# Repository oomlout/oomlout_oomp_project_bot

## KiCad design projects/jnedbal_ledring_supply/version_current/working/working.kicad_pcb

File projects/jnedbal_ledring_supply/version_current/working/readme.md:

# LEDring_supply by jnedbal  
This is a harvested standardized copy of a project from github.  
The original project can be found at:  
https://github.com/jnedbal/LEDring_supply  
Please consult that link for additional, details, files, and license information.  
Note: It was auto harvested and if the original repo had more than one board file or anything out of the ordinary the files here are likely not representative.

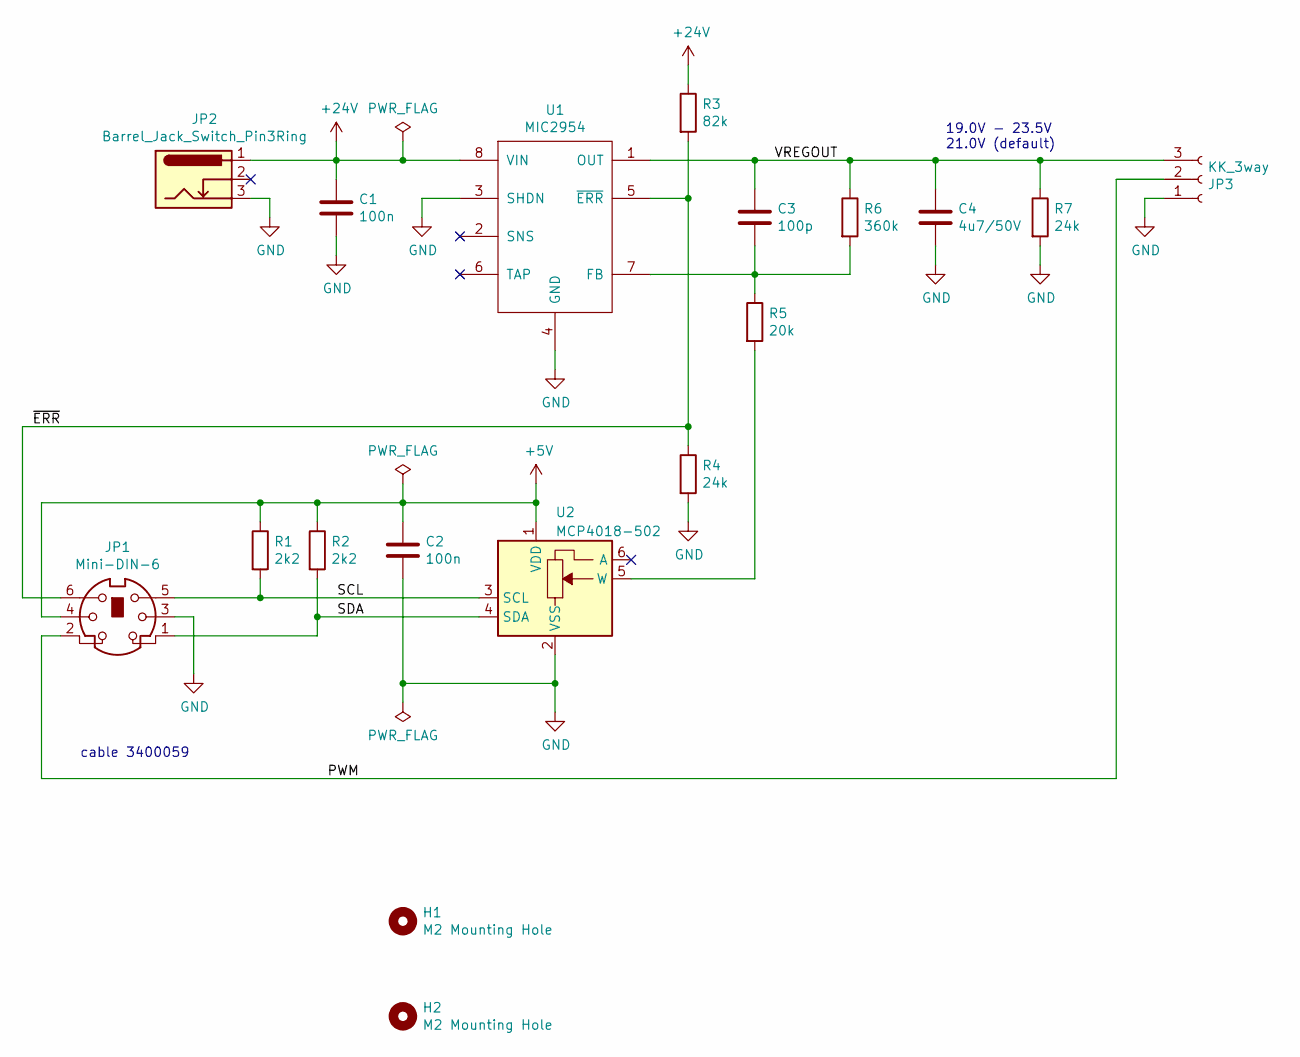
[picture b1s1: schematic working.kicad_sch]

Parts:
C1, C2: 100n; C_0603_1608Metric; Part Number MC0603B104K500CT
C3: 100p; C_0603_1608Metric; Part Number MC0603B101K500CT
C4: 4u7/50V; C_1206_3216Metric; Part Number GRM31CR71H475KA12L
H1, H2: M2 Mounting Hole; MountingHole_2.2mm_M2
JP1: Mini-DIN-6; MiniDIN6way; Part Number PSG01567
JP2: Barrel_Jack_Switch_Pin3Ring; 2.1mmBarrelJackTop; Part Number FC681473
JP3: KK_3way; Molex_KK-254_AE-6410-03A_1x03_P2.54mm_Vertical; Part Number 22-27-2031
R1, R2: 2k2; R_0603_1608Metric; Part Number MCWR06X2201FTL
R3: 82k; R_0603_1608Metric; Part Number MCWR06X8202FTL
R4: 24k; R_0603_1608Metric; Part Number MCWR06X2002FTL
R5: 20k; R_0603_1608Metric; Part Number MCWR06X2002FTL
R6: 360k; R_0603_1608Metric; Part Number MCWR06X3603FTL
R7: 24k; R_0603_1608Metric; Part Number MCWR06X2402FTL
U1: MIC2954; SO-8_3.9x4.9mm_P1.27mm; Part Number MIC2954-08YM
U2: MCP4018-502; SOT-363_SC-70-6; Part Number MCP4018T-502E/LT

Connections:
+5V: C2.1, JP1.4, R1.1, R2.1, U2.1 (VDD)
+24V: C1.1, JP2.1, R3.1, U1.8 (VIN)
/PWM: JP1.2, JP3.2
/SCL: JP1.5, R1.2, U2.3 (SCL)
/SDA: JP1.1, R2.2, U2.4 (SDA)
/VREGOUT: C3.1, C4.1, JP3.3, R6.1, R7.1, U1.1 (OUT)
/~ERR: JP1.6, R3.2, R4.1, U1.5 (~ERR)
GND: C1.2, C2.2, C4.2, JP1.3, JP2.3, JP3.1, R4.2, R7.2, U1.3 (SHDN), U1.4 (GND), U2.2 (VSS)
unnamed: C3.2, R5.1, R6.2, U1.7 (FB)
unnamed: R5.2, U2.5 (W)

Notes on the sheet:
19.0V - 23.5V 21.0V (default)
cable 3400059

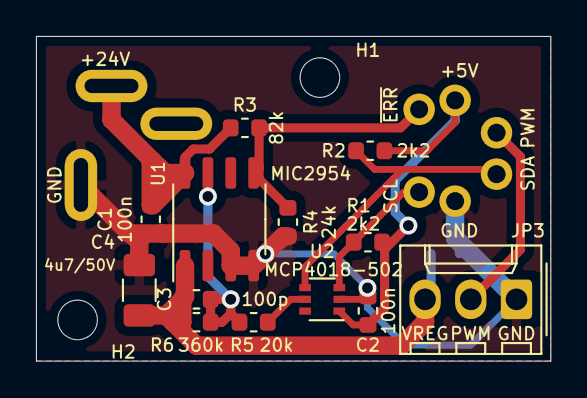
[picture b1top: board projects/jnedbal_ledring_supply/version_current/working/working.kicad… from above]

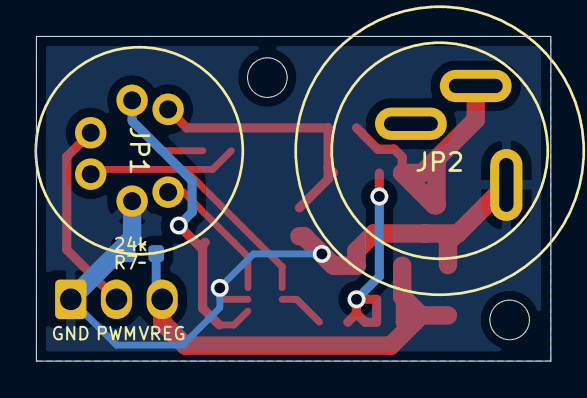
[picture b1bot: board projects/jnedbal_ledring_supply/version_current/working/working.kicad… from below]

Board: 2 copper layers, 28.6 x 18.0 mm, 18 parts (3 on the bottom side), 10 nets.

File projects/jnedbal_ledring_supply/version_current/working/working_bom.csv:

"Id";"Designator";"Footprint";"Quantity";"Designation";"Supplier and ref";
1;"R2,R1";"R_0603_1608Metric";2;"2k2";;;
2;"JP3";"Molex_KK-254_AE-6410-03A_1x03_P2.54mm_Vertical";1;"KK_3way";;;
3;"R7,R4";"R_0603_1608Metric";2;"24k";;;
4;"JP1";"MiniDIN6way";1;"Mini-DIN-6";;;
5;"C1,C2";"C_0603_1608Metric";2;"100n";;;
6;"C3";"C_0603_1608Metric";1;"100p";;;
7;"C4";"C_1206_3216Metric";1;"4u7/50V";;;
8;"JP2";"2.1mmBarrelJackTop";1;"Barrel_Jack_Switch_Pin3Ring";;;
9;"R3";"R_0603_1608Metric";1;"82k";;;
10;"R5";"R_0603_1608Metric";1;"20k";;;
11;"R6";"R_0603_1608Metric";1;"360k";;;
12;"U1";"SO-8_3.9x4.9mm_P1.27mm";1;"MIC2954";;;
13;"U2";"SOT-363_SC-70-6";1;"MCP4018-502";;;

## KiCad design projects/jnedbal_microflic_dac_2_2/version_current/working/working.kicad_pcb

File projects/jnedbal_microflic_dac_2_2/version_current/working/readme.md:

# OOMP Project  
## MicroFLiC_DAC_2_2  by jnedbal  
  
oomp key: oomp_projects_flat_jnedbal_microflic_dac_2_2  
(snippet of original readme)  

  full source readme at [readme_src.md](readme_src.md)  
  
source repo at: [https://github.com/jnedbal/MicroFLiC_DAC_2_2](https://github.com/jnedbal/MicroFLiC_DAC_2_2)  
## Board  

## Schematic  

[schematic pdf](working_schematic.pdf)  
## Images

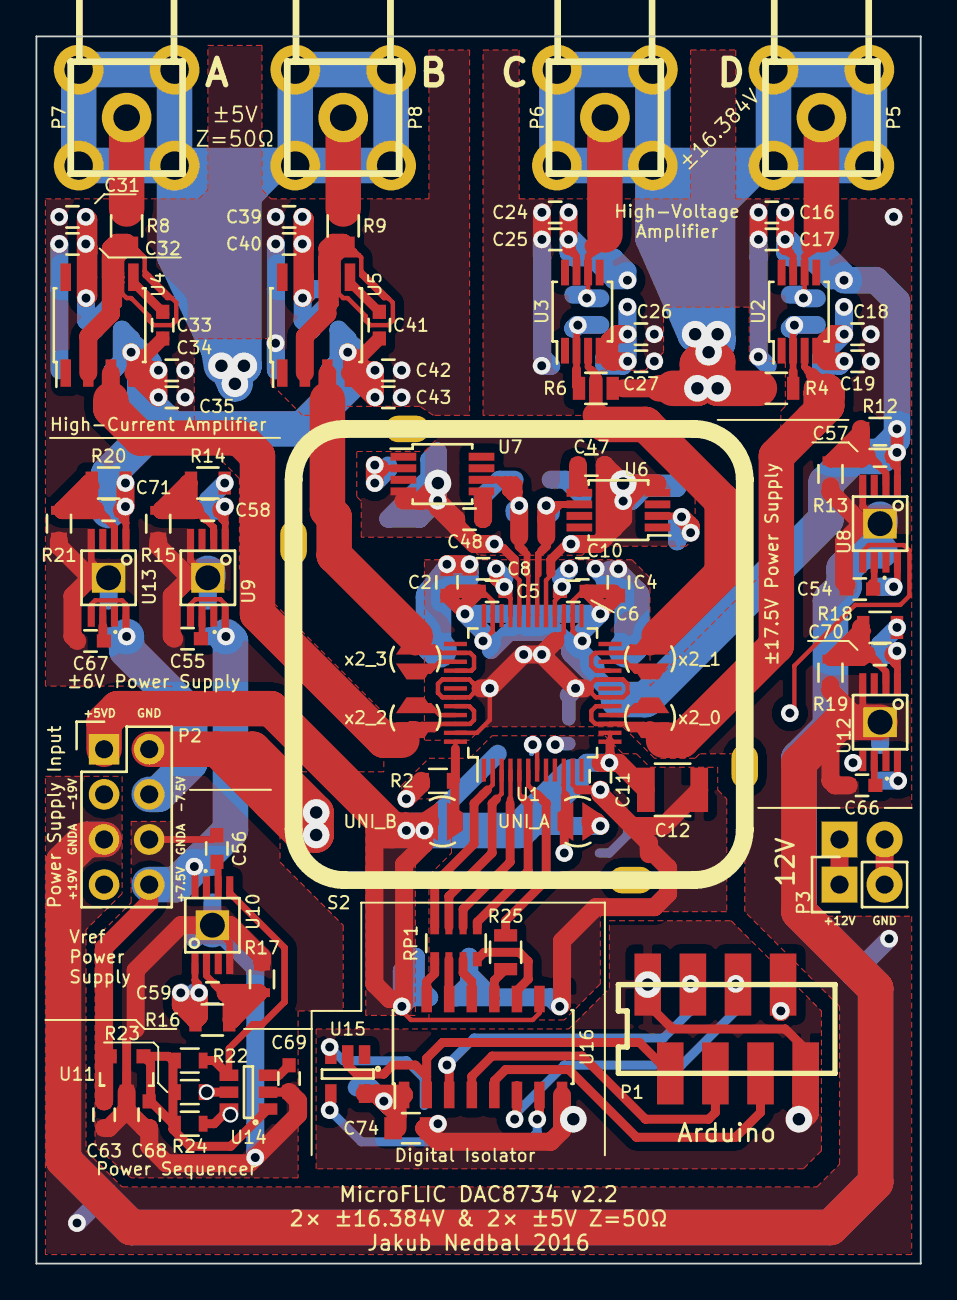
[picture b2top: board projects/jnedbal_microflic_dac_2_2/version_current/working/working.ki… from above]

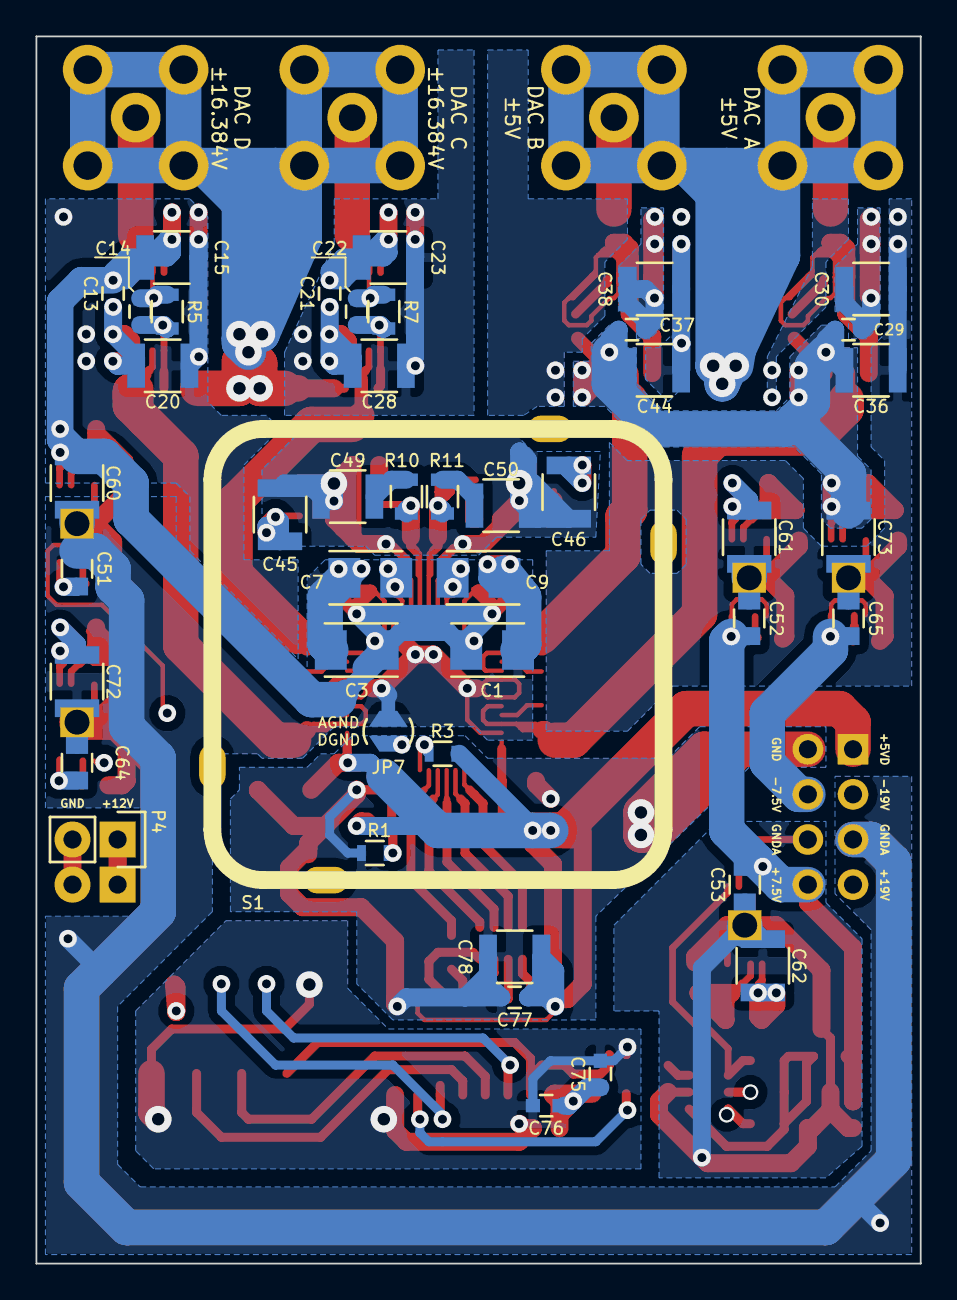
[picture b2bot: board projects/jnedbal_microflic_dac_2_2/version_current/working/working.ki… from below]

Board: 4 copper layers, 49.8 x 69.1 mm, 137 parts (45 on the bottom side), 74 nets.

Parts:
C1, C3, C7, C9: 4u7/25V; TantalC_SizeB_EIA-3528_Reflow
C2, C4, C8, C10, C11, C16, C19, C24, C27, C31, C35, C39, C43, C63, C68, C75, C76, C77: 100n; C_0603
C5, C6, C13, C17, C18, C21, C25, C26, C29, C32, C34, C37, C40, C42, C54, C55, C56, C57, C58, C59, C66, C67, C70, C71: 10n; C_0603
C12, C30, C36, C38, C44, C45, C46, C49, C50, C61, C62, C73, C78: 22u/25V; C_1210
C14, C22, C33, C41: 10p; C_0603
C15, C20, C23, C28, C60, C72: 10u/35V; C_1210
C47, C48, C69: 1u/25V; C_0603
C51, C52, C53, C64, C65, C74: 10u/25V; C_0805
JP1: UNI_A; solder_jumper
JP2: UNI_B; solder_jumper
JP3: x2_0; solder_jumper
JP4: x2_1; solder_jumper
JP5: x2_2; solder_jumper
JP6: x2_3; solder_jumper
JP7: GND/GNDA; solder_jumper
P1: 8-way Micro-MaTch; 7-188275-8
P2: 2x4 header strip; Pin_Header_Straight_2x04
P3: 1x2 header strip; Pin_Header_Straight_1x02
P4: 1x2 socket strip; Socket_Strip_Straight_1x02
P5, P6, P7, P8: SMA
R1, R2, R3, R13, R15, R17, R19, R21, R22, R23, R24: 12k; R_0603
R4, R5, R6, R7: 1k/0.01%/100mW; R_0805
R8, R9: 49R9/0.1%/250mW; R_0805
R10, R11: 1; R_0805
R12, R18: 165k; R_0805
R14, R16, R20: 48k7; R_0805
R25: 150; R_0805
RP1: 4x150; R_Array_Convex_4x0603
S1, S2: shield_can; can-MS257-10
U1: DAC8734; TQFP-48_7x7mm_Pitch0.5mm
U2, U3: OPA211; MSOP-8_3x3mm_Pitch0.65mm
U4, U5: AD8021; SOIC-8_3.9x4.9mm_Pitch1.27mm
U6: REF5040; MSOP-8_3x3mm_Pitch0.65mm
U7: REF5050; MSOP-8_3x3mm_Pitch0.65mm
U8, U9, U10: TPS7A4901; SSOP8_powerPAD
U11: LM3480; SOT-23
U12, U13: TPS7A3001; SSOP8_powerPAD
U14: LM3880; SOT-23-6
U15: 74AHC1G14; SOT-23-5
U16: Si8651; SOIC-16_3.9x9.9mm_Pitch1.27mm

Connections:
+5V: C68.1, R22.2, R23.2, R24.2, U11.1, U14.1
+5VD: C11.1, C12.1, C77.1, C78.1, JP1.2, JP2.2, P2.1, R3.2, U1.13, U1.14, U16.10, U16.16
+6V: C29.1, C30.2, C31.2, C32.2, C37.1, C38.2, C39.2, C40.2, C58.1, C61.1, R14.1, U4.7, U5.7, U9.1
-6V: C29.2, C33.2, C34.2, C35.2, C36.2, C37.2, C41.2, C42.2, C43.2, C44.2, C71.1, C73.1, R20.1, U4.4, U5.4, U13.1
/P12V: P3.1, P4.1
/PGND: P3.2, P4.2
/digitalIsolation/A_GND: C74.2, C75.2, C76.2, P1.1, P1.8, U15.3, U16.8
/digitalIsolation/A_IOREF: C74.1, C75.1, C76.1, P1.7, U15.5, U16.1
/digitalIsolation/A_SCLK: P1.3, U16.3
/digitalIsolation/A_SDI: P1.4, U16.4
/digitalIsolation/A_SDO: P1.5, U16.6
/digitalIsolation/A_~LDAC: P1.6, U16.5
/digitalIsolation/A_~SS: P1.2, U15.2, U16.2
/digitalIsolation/SCLK: RP1.7, U1.3
/digitalIsolation/SDI: RP1.6, U1.4
/digitalIsolation/SDO: RP1.5, U1.5
/digitalIsolation/~LDAC: R25.1, U1.6
/digitalIsolation/~SS: RP1.8, U1.2
/highCurrentAmp/CMP1: C41.1, U5.5
/highCurrentAmp/CMP2: C33.1, U4.5
/highCurrentAmp/INV-2: R8.2, U4.2, U4.6
/highCurrentAmp/INV-3: R9.2, U5.2, U5.6
/highCurrentAmp/VOUT-2: JP5.2, U1.44, U1.46, U4.3
/highCurrentAmp/VOUT-3: JP6.2, U1.38, U1.40, U5.3
/highCurrentAmp/VOUT-C: P7.1, R8.1
/highCurrentAmp/VOUT-D: P8.1, R9.1
/highVoltageAmp/INV-0: C14.2, R4.1, R5.2, U2.2
/highVoltageAmp/INV-1: C22.2, R6.1, R7.2, U3.2
/highVoltageAmp/VOUT-0: JP3.2, U1.15, U1.17, U2.3
/highVoltageAmp/VOUT-1: JP4.2, U1.21, U1.23, U3.3
/highVoltageAmp/VOUT-A: C14.1, P5.1, R5.1, U2.6
/highVoltageAmp/VOUT-B: C22.1, P6.1, R7.1, U3.6
/powerSupply/+7.5V: C52.1, C53.1, C63.1, P2.8, U9.5, U9.8, U10.8, U11.2
/powerSupply/+19V: C51.1, P2.7, U8.8
/powerSupply/-7.5V: C65.1, P2.4, U13.5, U13.8
/powerSupply/-19V: C64.1, P2.3, U12.8
/powerSupply/EN_REF: R22.1, U10.5, U14.4
/powerSupply/EN_VDD: R23.1, U8.5, U14.5
/powerSupply/EN_VSS: R24.1, U12.5, U14.6
/powerSupply/FB+6: C58.2, R14.2, R15.1, U9.2
/powerSupply/FB-6: C71.2, R20.2, R21.1, U13.2
/powerSupply/FBREF: C59.2, R16.2, R17.1, U10.2
/powerSupply/FBVDD: C57.2, R12.2, R13.1, U8.2
/powerSupply/FBVSS: C70.2, R18.2, R19.1, U12.2
/powerSupply/NR+6: C55.1, U9.6
/powerSupply/NR-6: C67.1, U13.6
/powerSupply/NRREF: C56.1, U10.6
/powerSupply/NRVDD: C54.1, U8.6
/powerSupply/NRVSS: C66.1, U12.6
/reference/4.096V: R10.1, U1.30, U6.6
/reference/5.000V: R11.1, U1.31, U7.6
/reference/TRIM4: C47.1, U6.5
/reference/TRIM5: C48.1, U7.5
GND: C11.2, C12.2, C77.2, C78.2, JP7.1, P2.2, R1.2, R2.2, U1.11, U16.9
GNDA: C1.2, C2.2, C3.2, C4.2, C7.1, C8.2, C9.1, C10.2, C15.1, C16.1, C17.1, C18.1, C19.1, C20.1, C23.1, C24.1, C25.1, C26.1, C27.1, C28.1, C30.1, C31.1, C32.1, C34.1, C35.1, C36.1, C38.1, C39.1, C40.1, C42.1, C43.1, C44.1, C45.2, C46.2, C47.2, C48.2, C49.2, C50.2, C51.2, C52.2, C53.2, C54.2, C55.2, C56.2, C60.2, C61.2, C62.2, C63.2, C64.2, C65.2, C66.2, C67.2, C68.2, C69.2, C72.2, C73.2, JP7.2, P2.5, P2.6, P5.2, P5.3, P5.4, P5.5, P6.2, P6.3, P6.4, P6.5, P7.2, P7.3, P7.4, P7.5, P8.2, P8.3, P8.4, P8.5, R4.2, R6.2, R13.2, R15.2, R17.2, R19.2, R21.2, S1.1, S2.2, U1.18, U1.20, U1.27, U1.29, U1.32, U1.41, U1.43, U1.47, U6.4, U7.4, U8.4, U8.9, U9.4, U9.9, U10.4, U10.9, U11.3, U12.4, U12.9, U13.4, U13.9, U14.2
unnamed: C49.1, R10.2
unnamed: C50.1, R11.2
unnamed: C69.1, U14.3
unnamed: JP1.1, R1.1, U1.10
unnamed: JP2.1, R2.1, U1.48
unnamed: JP3.1, U1.16
unnamed: JP4.1, U1.22
unnamed: JP5.1, U1.45
unnamed: JP6.1, U1.39
unnamed: R3.1, U1.7
unnamed: R25.2, U16.12
unnamed: RP1.1, U16.15
unnamed: RP1.2, U16.14
unnamed: RP1.3, U16.13
unnamed: RP1.4, U16.11
unnamed: U15.4, U16.7
VCC: C45.1, C46.1, C59.1, C62.1, R16.1, U6.2, U7.2, U10.1
VDD: C1.1, C2.1, C3.1, C4.1, C5.1, C6.1, C13.1, C15.2, C16.2, C17.2, C21.1, C23.2, C24.2, C25.2, C57.1, C60.1, R12.1, U1.26, U1.35, U2.7, U3.7, U8.1
VSS: C5.2, C6.2, C7.2, C8.1, C9.2, C10.1, C13.2, C18.2, C19.2, C20.2, C21.2, C26.2, C27.2, C28.2, C70.1, C72.1, R18.1, U1.28, U1.33, U2.4, U3.4, U12.1

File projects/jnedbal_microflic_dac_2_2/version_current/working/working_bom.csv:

"Id";"Designator";"Footprint";"Quantity";"Designation";"Supplier and ref";
1;"P5,P6,P7,P8";"SMA";4;"SMA";;;
2;"U12,U13";"SSOP8_powerPAD";2;"TPS7A3001";;;
3;"C54,C56,C59,C57,C70,C66,C18,C13,C17,C25,C34,C29,C32,C40,C5,C6,C21,C37,C42,C55,C58,C67,C71,C26";"C_0603";24;"10n";;;
4;"C53,C51,C64,C52,C65,C74";"C_0805";6;"10u/25V";;;
5;"R16,R14,R20";"R_0805";3;"48k7";;;
6;"U10,U8,U9";"SSOP8_powerPAD";3;"TPS7A4901";;;
7;"C62,C36,C30,C12,C45,C46,C49,C50,C61,C73,C38,C44,C78";"C_1210";13;"22u/25V";;;
8;"C60,C72,C20,C15,C23,C28";"C_1210";6;"10u/35V";;;
9;"R12,R18";"R_0805";2;"165k";;;
10;"JP1";"solder_jumper";1;"UNI_A";;;
11;"P2";"Pin_Header_Straight_2x04";1;"2x4 header strip";;;
12;"C19,C16,C35,C31,C2,C4,C8,C10,C11,C24,C27,C39,C43,C77,C75,C63,C68,C76";"C_0603";18;"100n";;;
13;"U2,U3";"MSOP-8_3x3mm_Pitch0.65mm";2;"OPA211";;;
14;"R5,R4,R6,R7";"R_0805";4;"1k/0.01%/100mW";;;
15;"C14,C22,C33,C41";"C_0603";4;"10p";;;
16;"R8,R9";"R_0805";2;"49R9/0.1%/250mW";;;
17;"U4,U5";"SOIC-8_3.9x4.9mm_Pitch1.27mm";2;"AD8021";;;
18;"U7";"MSOP-8_3x3mm_Pitch0.65mm";1;"REF5050";;;
19;"P1";"7-188275-8";1;"8-way Micro-MaTch";;;
20;"U14";"SOT-23-6";1;"LM3880";;;
21;"U1";"TQFP-48_7x7mm_Pitch0.5mm";1;"DAC8734";;;
22;"U15";"SOT-23-5";1;"74AHC1G14";;;
23;"U16";"SOIC-16_3.9x9.9mm_Pitch1.27mm";1;"Si8651";;;
24;"C1,C3,C7,C9";"TantalC_SizeB_EIA-3528_Reflow";4;"4u7/25V";;;
25;"C47,C48,C69";"C_0603";3;"1u/25V";;;
26;"JP6";"solder_jumper";1;"x2_3";;;
27;"JP5";"solder_jumper";1;"x2_2";;;
28;"JP4";"solder_jumper";1;"x2_1";;;
29;"JP3";"solder_jumper";1;"x2_0";;;
30;"JP2";"solder_jumper";1;"UNI_B";;;
31;"U6";"MSOP-8_3x3mm_Pitch0.65mm";1;"REF5040";;;
32;"P3";"Pin_Header_Straight_1x02";1;"1x2 header strip";;;
33;"P4";"Socket_Strip_Straight_1x02";1;"1x2 socket strip";;;
34;"R10,R11";"R_0805";2;"1";;;
35;"RP1";"R_Array_Convex_4x0603";1;"4x150";;;
36;"R25";"R_0805";1;"150";;;
37;"JP7";"solder_jumper";1;"GND/GNDA";;;
38;"U11";"SOT-23";1;"LM3480";;;
39;"S1,S2";"can-MS257-10";2;"shield_can";;;
40;"R24,R22,R13,R15,R17,R23,R19,R21,R1,R2,R3";"R_0603";11;"12k";;;

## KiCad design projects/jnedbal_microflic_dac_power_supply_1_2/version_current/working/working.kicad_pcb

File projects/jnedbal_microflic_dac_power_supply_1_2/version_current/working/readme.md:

# OOMP Project  
## MicroFLiC_DAC_power_supply_1_2  by jnedbal  
  
oomp key: oomp_projects_flat_jnedbal_microflic_dac_power_supply_1_2  
(snippet of original readme)  

  full source readme at [readme_src.md](readme_src.md)  
  
source repo at: [https://github.com/jnedbal/MicroFLiC_DAC_power_supply_1_2](https://github.com/jnedbal/MicroFLiC_DAC_power_supply_1_2)  
## Board  

## Schematic  

[schematic pdf](working_schematic.pdf)  
## Images

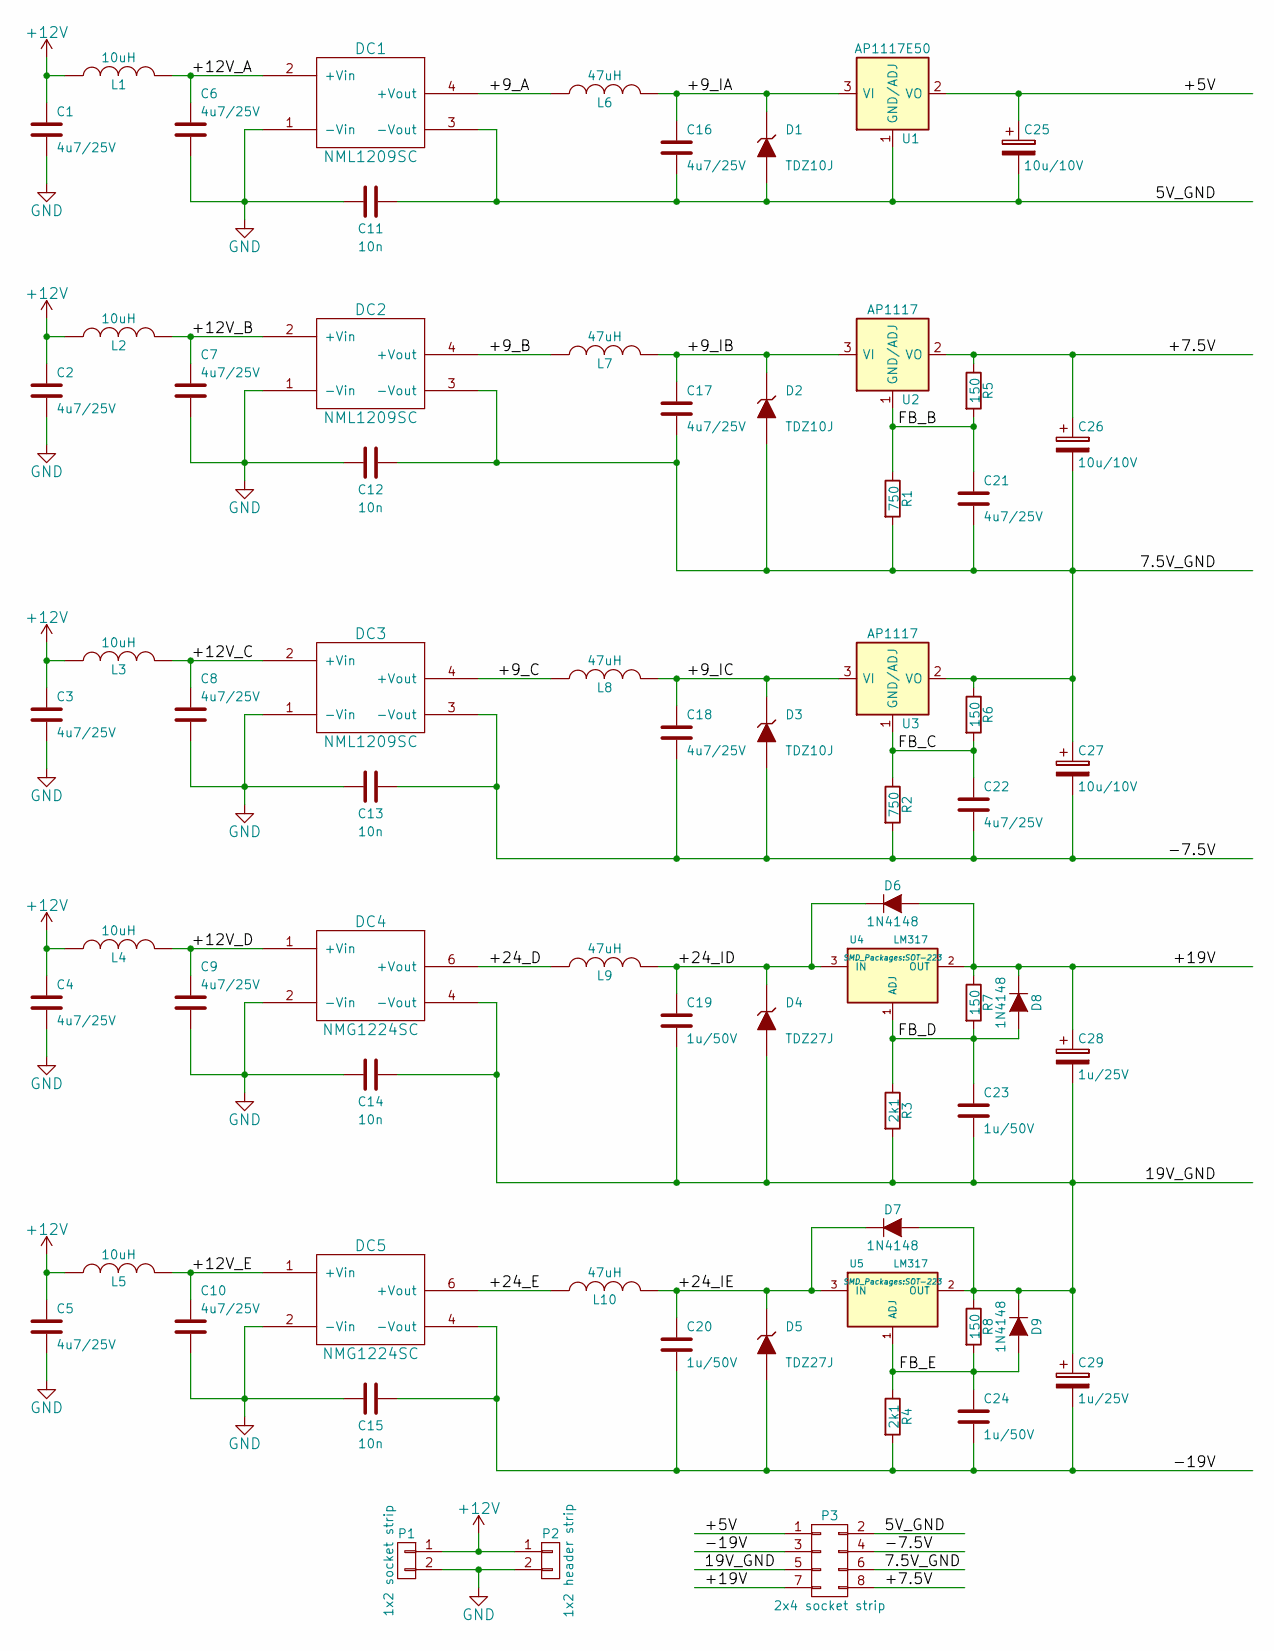
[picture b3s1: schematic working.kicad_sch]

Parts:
C1, C2, C3, C4, C5, C6, C7, C8, C9, C10, C16, C17, C18, C21, C22: 4u7/25V; C_0805; Part Number GRM21BR61E475MA12L
C11, C12, C13, C14, C15: 10n; C_0805; Part Number MCU0805R103KCT
C19, C20, C23, C24: 1u/50V; C_0805; Part Number GRM219R61H105KA73D
C25, C26, C27: 10u/10V; TantalC_SizeA_EIA-3216_Reflow; Part Number TAJA106K010RNJ
C28, C29: 1u/25V; TantalC_SizeA_EIA-3216_Reflow; Part Number TRJA105K025RRJ
D1, D2, D3: TDZ10J; SOD-323_Zener; Part Number TDZ10J
D4, D5: TDZ27J; SOD-323_Zener; Part Number TDZ27J
D6, D7, D8, D9: 1N4148; SOD-323; Part Number 1N4148WS
DC1, DC2, DC3: NML1209SC; MurataNML; Part Number NML1209SC
DC4, DC5: NMG1224SC; MurataNMG; Part Number NMG1224SC
L1, L2, L3, L4, L5: 10uH; murata8200coil; Part Number 7440329100
L6, L7, L8, L9, L10: 47uH; murata8200coil; Part Number 82473C
P1: 1x2 socket strip; ESQ-102-33-G-S; Part Number ESQ-102-33-G-S
P2: 1x2 header strip; Pin_Header_Straight_1x02; Part Number M20-9990245
P3: 2x4 socket strip; ESQ-104-33-G-D; Part Number ESQ-104-33-G-D
R1, R2: 750; R_0805; Part Number MCMR08X7500FTL
R3, R4: 2k1; R_0805; Part Number CRCW08052K10FKEA
R5, R6, R7, R8: 150; R_0805; Part Number MCWR08X1500FTL
U1: AP1117E50; SOT-223; Part Number AP1117E50G-13
U2, U3: AP1117; SOT-223; Part Number AP1117EG-13
U4, U5: LM317; SOT-223; Part Number LM317DCY

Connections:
+12V: C1.1, C2.1, C3.1, C4.1, C5.1, L1.1, L2.1, L3.1, L4.1, L5.1, P1.1, P2.1
/5V_GND: C11.1, C16.2, C25.2, D1.2 (A), DC1.3 (-Vout), P3.2, U1.1 (GND/ADJ)
/7.5V_GND: C12.1, C17.2, C21.2, C26.2, C27.1, D2.2 (A), DC2.3 (-Vout), P3.6, R1.2, R6.1, U3.2 (VO)
/19V_GND: C14.1, C19.2, C23.2, C28.2, C29.1, D4.2 (A), D7.2 (A), D9.1 (K), DC4.4 (-Vout), P3.5, R3.2, R8.1, U5.2 (OUT)
/+5V: C25.1, P3.1, U1.2 (VO)
/+7.5V: C26.1, P3.8, R5.1, U2.2 (VO)
/+9_A: DC1.4 (+Vout), L6.1
/+9_B: DC2.4 (+Vout), L7.1
/+9_C: DC3.4 (+Vout), L8.1
/+9_IA: C16.1, D1.1 (K), L6.2, U1.3 (VI)
/+9_IB: C17.1, D2.1 (K), L7.2, U2.3 (VI)
/+9_IC: C18.1, D3.1 (K), L8.2, U3.3 (VI)
/+12V_A: C6.1, DC1.2 (+Vin), L1.2
/+12V_B: C7.1, DC2.2 (+Vin), L2.2
/+12V_C: C8.1, DC3.2 (+Vin), L3.2
/+12V_D: C9.1, DC4.1 (+Vin), L4.2
/+12V_E: C10.1, DC5.1 (+Vin), L5.2
/+19V: C28.1, D6.2 (A), D8.1 (K), P3.7, R7.1, U4.2 (OUT)
/+24_D: DC4.6 (+Vout), L9.1
/+24_E: DC5.6 (+Vout), L10.1
/+24_ID: C19.1, D4.1 (K), D6.1 (K), L9.2, U4.3 (IN)
/+24_IE: C20.1, D5.1 (K), D7.1 (K), L10.2, U5.3 (IN)
/-7.5V: C13.1, C18.2, C22.2, C27.2, D3.2 (A), DC3.3 (-Vout), P3.4, R2.2
/-19V: C15.1, C20.2, C24.2, C29.2, D5.2 (A), DC5.4 (-Vout), P3.3, R4.2
/FB_B: C21.1, R1.1, R5.2, U2.1 (GND/ADJ)
/FB_C: C22.1, R2.1, R6.2, U3.1 (GND/ADJ)
/FB_D: C23.1, D8.2 (A), R3.1, R7.2, U4.1 (ADJ)
/FB_E: C24.1, D9.2 (A), R4.1, R8.2, U5.1 (ADJ)
GND: C1.2, C2.2, C3.2, C4.2, C5.2, C6.2, C7.2, C8.2, C9.2, C10.2, C11.2, C12.2, C13.2, C14.2, C15.2, DC1.1 (-Vin), DC2.1 (-Vin), DC3.1 (-Vin), DC4.2 (-Vin), DC5.2 (-Vin), P1.2, P2.2

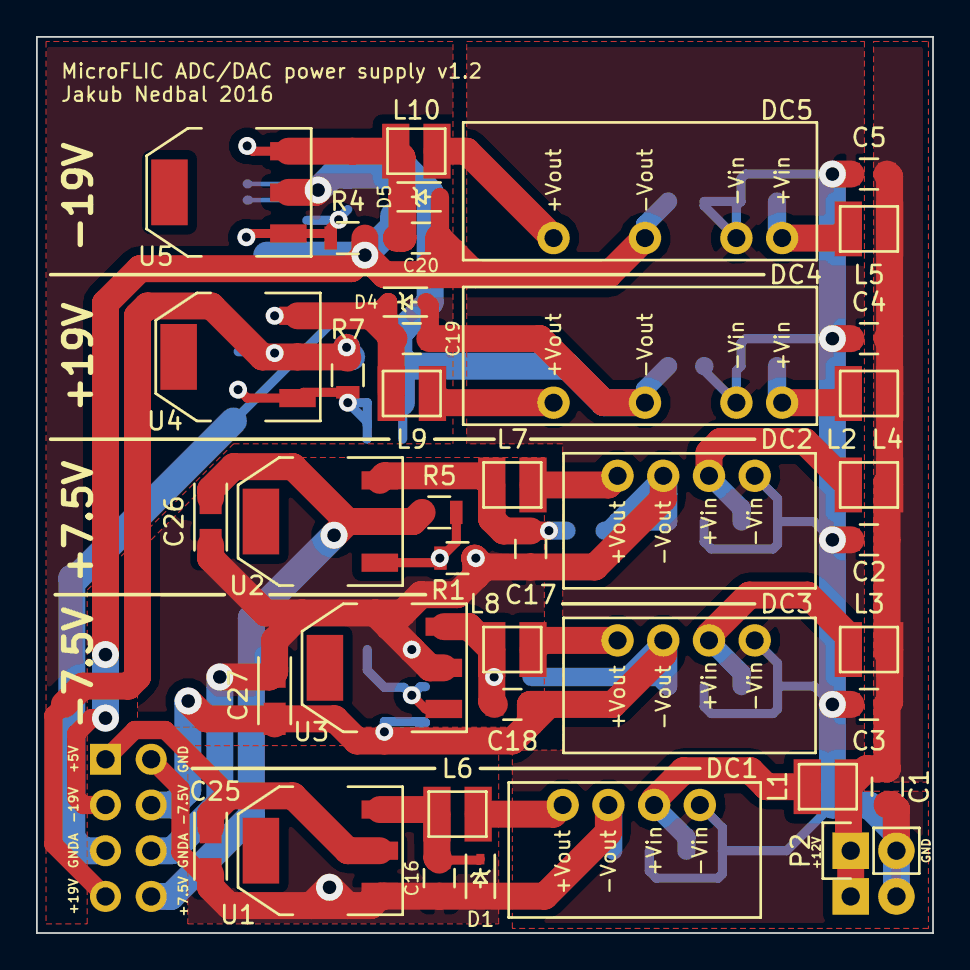
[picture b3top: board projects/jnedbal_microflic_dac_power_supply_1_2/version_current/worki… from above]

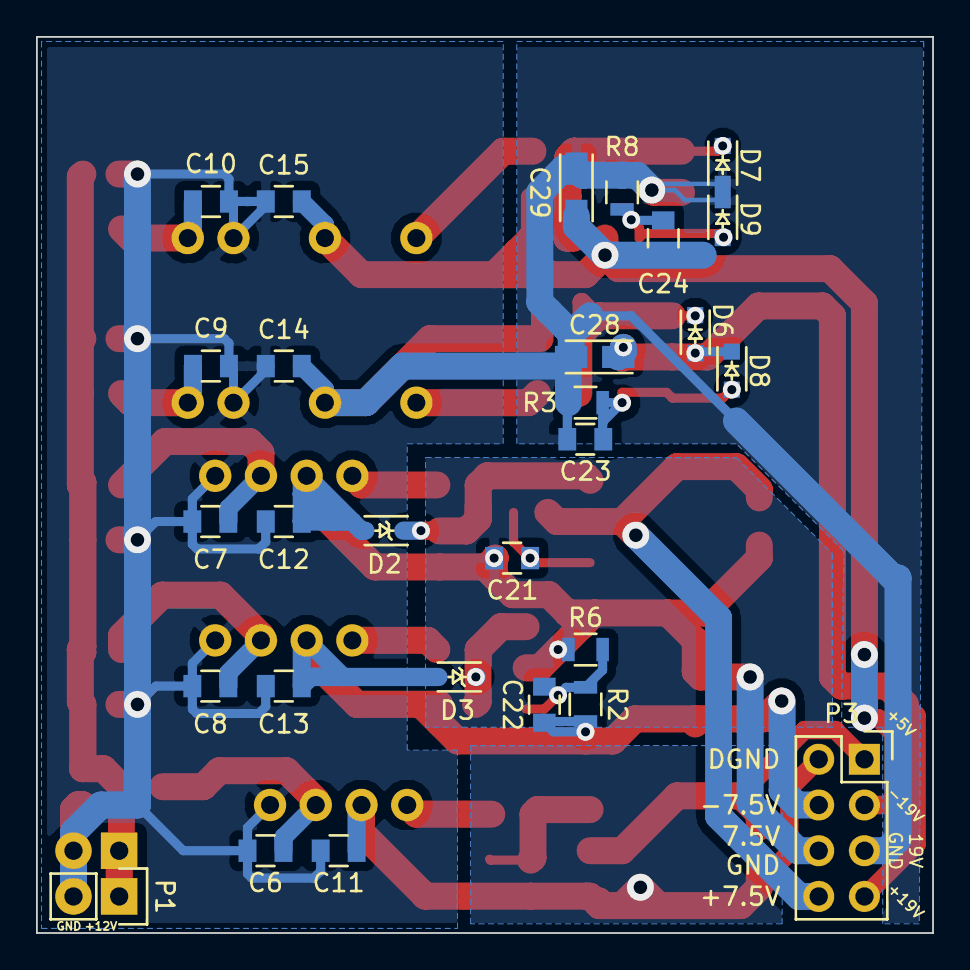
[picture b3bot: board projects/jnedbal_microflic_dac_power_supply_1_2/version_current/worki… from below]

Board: 2 copper layers, 49.8 x 49.8 mm, 69 parts (28 on the bottom side), 29 nets.

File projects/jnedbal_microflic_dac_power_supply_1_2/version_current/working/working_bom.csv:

"Id";"Designator";"Footprint";"Quantity";"Designation";"Supplier and ref";
1;"C1,C2,C3,C4,C5,C16,C17,C18,C6,C7,C8,C9,C10,C21,C22";"C_0805";15;"4u7/25V";;;
2;"C11,C12,C13,C14,C15";"C_0805";5;"10n";;;
3;"C19,C20,C23,C24";"C_0805";4;"1u/50V";;;
4;"C25,C27,C26";"TantalC_SizeA_EIA-3216_Reflow";3;"10u/10V";;;
5;"C28,C29";"TantalC_SizeA_EIA-3216_Reflow";2;"1u/25V";;;
6;"DC1,DC2,DC3";"MurataNML";3;"NML1209SC";;;
7;"DC4,DC5";"MurataNMG";2;"NMG1224SC";;;
8;"L1,L2,L3,L4,L5";"murata8200coil";5;"10uH";;;
9;"L6,L7,L8,L9,L10";"murata8200coil";5;"47uH";;;
10;"R1,R2";"R_0805";2;"750";;;
11;"R3,R4";"R_0805";2;"2k1";;;
12;"R5,R7,R8,R6";"R_0805";4;"150";;;
13;"U4,U5";"SOT-223";2;"LM317";;;
14;"U1";"SOT-223";1;"AP1117E50";;;
15;"U2,U3";"SOT-223";2;"AP1117";;;
16;"P1";"ESQ-102-33-G-S";1;"1x2 socket strip";;;
17;"P3";"ESQ-104-33-G-D";1;"2x4 socket strip";;;
18;"P2";"Pin_Header_Straight_1x02";1;"1x2 header strip";;;
19;"D5,D4";"SOD-323_Zener";2;"TDZ27J";;;
20;"D1,D3,D2";"SOD-323_Zener";3;"TDZ10J";;;
21;"D6,D7,D8,D9";"SOD-323";4;"1N4148";;;

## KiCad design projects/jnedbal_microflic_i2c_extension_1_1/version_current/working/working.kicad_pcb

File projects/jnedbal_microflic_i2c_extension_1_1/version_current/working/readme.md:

# MicroFLiC_I2C_extension_1_1 by jnedbal  
This is a harvested standardized copy of a project from github.  
The original project can be found at:  
https://github.com/jnedbal/MicroFLiC_I2C_extension_1_1  
Please consult that link for additional, details, files, and license information.  
Note: It was auto harvested and if the original repo had more than one board file or anything out of the ordinary the files here are likely not representative.

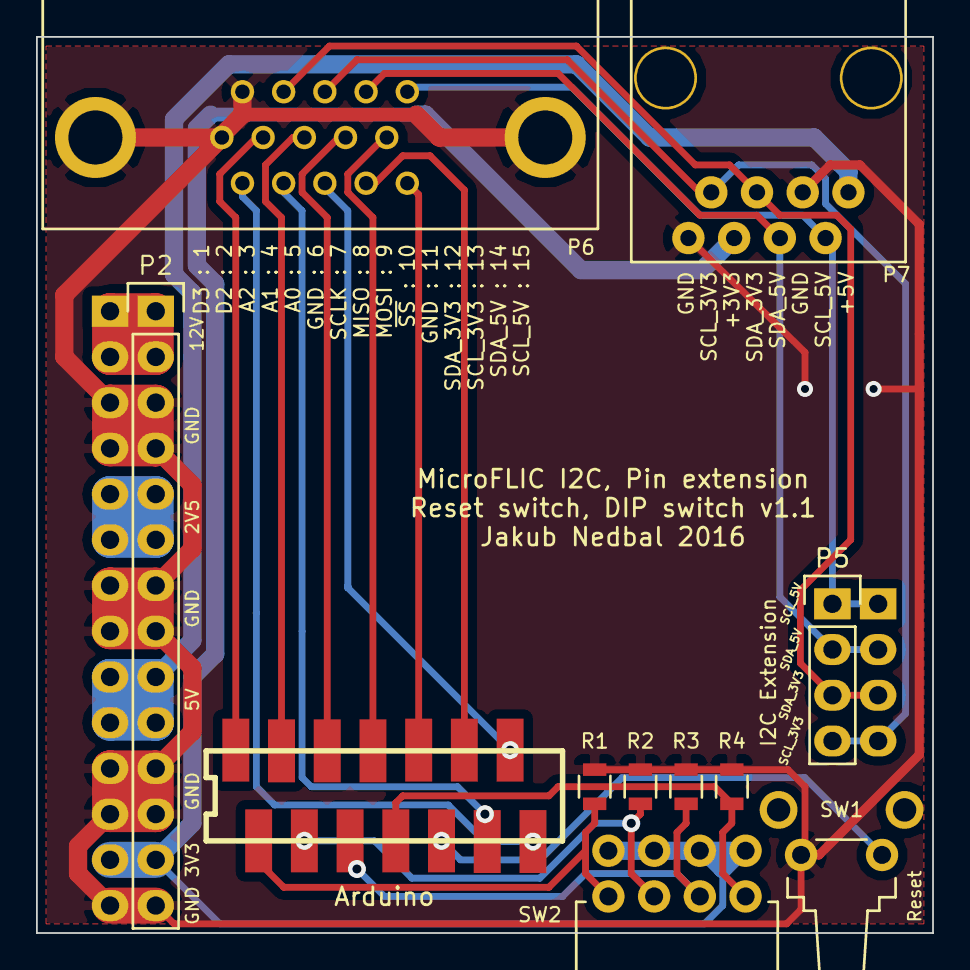
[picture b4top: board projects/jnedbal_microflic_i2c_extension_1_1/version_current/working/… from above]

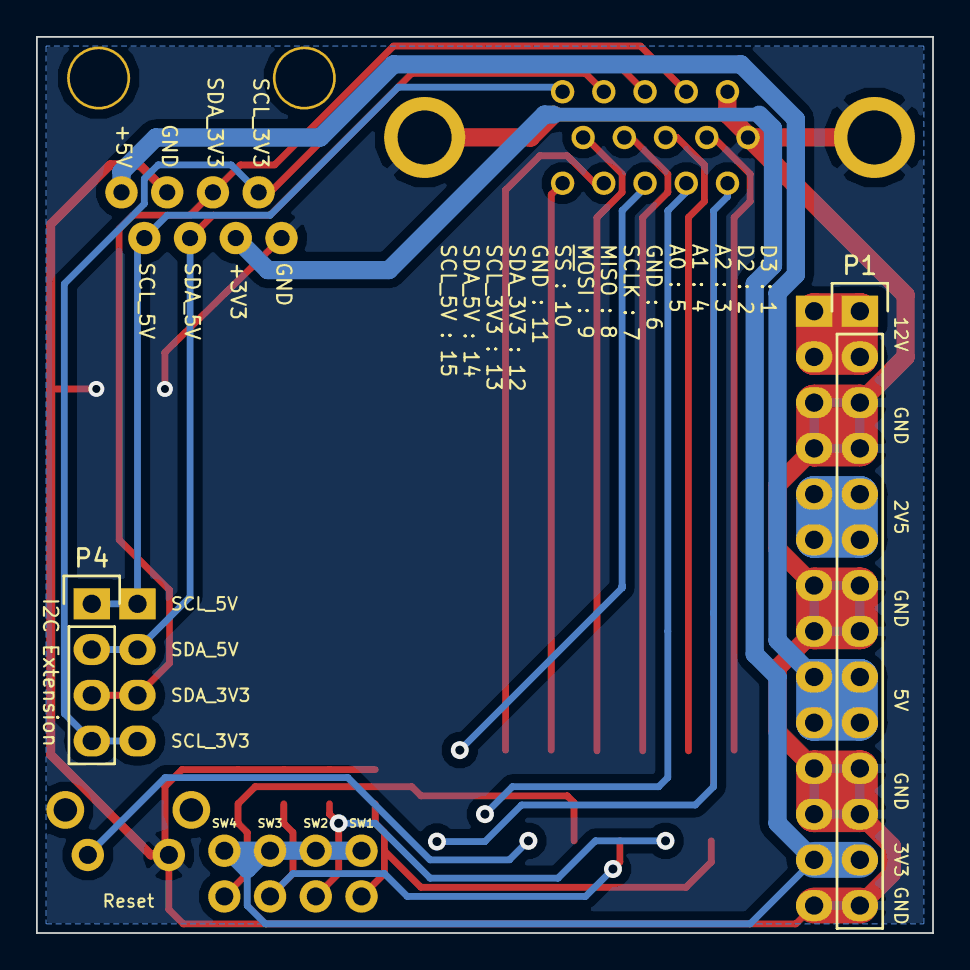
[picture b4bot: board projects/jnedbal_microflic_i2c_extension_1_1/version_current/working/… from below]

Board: 2 copper layers, 49.8 x 49.8 mm, 13 parts (2 on the bottom side), 23 nets.

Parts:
P1: 1x14 header strip; Pin_Header_Straight_1x14
P2: 1x14 socket strip; ESQ-114-33-G-S
P3: 14-way Micro-MaTch; 1-188275-4
P4: 1x4 header strip; Pin_Header_Straight_1x04
P5: 1x4 socket strip; ESQ-104-33-G-S
P6: DB15-VGA; dsub15
P7: RJ45
R1, R2, R3, R4: 10k; R_0805
SW1: Tactile switch R/A; tactileSwitchRA
SW2: DIPS_04; DIP4RA

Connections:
+2V5: P1.5, P1.6, P2.5, P2.6
+3V3: P1.13, P2.13, P7.6, SW2.5, SW2.6, SW2.7, SW2.8
+5VP: P1.9, P1.10, P2.9, P2.10, P7.1
+12V: P1.1, P1.2, P2.1, P2.2
/A0: P3.9, P6.5
/A1: P3.11, P6.4
/A2: P3.13, P6.3
/D2: P3.12, P6.2
/D3: P3.14, P6.1
/MISO: P3.3, P6.8
/MOSI: P3.5, P6.9
/RST: P3.10, SW1.1
/SCLK: P3.1, P6.7
/SCL_3V3: P4.4, P5.4, P6.13, P7.7
/SCL_5V: P4.1, P5.1, P6.15, P7.2
/SDA_3V3: P4.3, P5.3, P6.12, P7.5
/SDA_5V: P4.2, P5.2, P6.14, P7.4
/SW1: P3.2, R1.1, SW2.1
/SW2: P3.4, R2.1, SW2.2
/SW3: P3.6, R3.1, SW2.3
/SW4: P3.8, R4.1, SW2.4
/~SS: P3.7, P6.10
GND: P1.3, P1.4, P1.7, P1.8, P1.11, P1.12, P1.14, P2.3, P2.4, P2.7, P2.8, P2.11, P2.12, P2.14, P6.6, P6.11, P6.16, P6.17, P7.3, P7.8, R1.2, R2.2, R3.2, R4.2, SW1.2

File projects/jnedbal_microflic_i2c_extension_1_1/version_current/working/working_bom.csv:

"Id";"Designator";"Footprint";"Quantity";"Designation";"Supplier and ref";
1;"P7";"RJ45";1;"RJ45";;;
2;"R1,R2,R3,R4";"R_0805";4;"10k";;;
3;"SW1";"tactileSwitchRA";1;"Tactile switch R/A";;;
4;"SW2";"DIP4RA";1;"DIPS_04";;;
5;"P6";"dsub15";1;"DB15-VGA";;;
6;"P1";"Pin_Header_Straight_1x14";1;"1x14 header strip";;;
7;"P2";"ESQ-114-33-G-S";1;"1x14 socket strip";;;
8;"P3";"1-188275-4";1;"14-way Micro-MaTch";;;
9;"P4";"Pin_Header_Straight_1x04";1;"1x4 header strip";;;
10;"P5";"ESQ-104-33-G-S";1;"1x4 socket strip";;;
